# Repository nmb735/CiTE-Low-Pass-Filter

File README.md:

# 🎚️ CiTE: Fourth Order Low Pass Filter

Full implementation of a fourth-order low-pass filter. The circuit design is based on the use of two cascaded second-order Sallen-Key configurations. Presented as the final project for CiTE (*Circuits i Tecnologies Electròniques*), part of the third course of the Electronic Engineering degree (BSc).

## 👨‍💻 Developers

- Adrià Arús - @Addruss
- Nedal Benelmekki - @nmb735
- Marc Serra - @Marcits

## 📋 Context and Introduction

- This project involves the full implementation of a fourth-order low-pass filter. The circuit design is based on the use of two cascaded second-order Sallen-Key configurations. It was presented as the final project for CiTE (*Circuits i Tecnologies Electròniques*), part of the third course of the Electronic Engineering degree (BSc).

- The project encompassed the entire process, including circuit and PCB design, manufacturing, soldering, and testing.

## 📂 Content

This repository contains the full project in different directories:

1. **`EAGLE Project`**: Full PCB project (`EAGLE` software, from Autodesk), including Layout, Schematic, Gerber Files, BOM, and other related files.
2. **`Documentation`**: Project documentation and presentation poster.

## 📝 License

This project is licensed under the MIT License. See the LICENSE file for more details.

## ⚠️ Disclaimer

This project is provided for educational purposes only. The authors are not responsible for any use of this project in any form of academic dishonesty or plagiarism. Please adhere to your institution's academic integrity policies when using or referencing this project.

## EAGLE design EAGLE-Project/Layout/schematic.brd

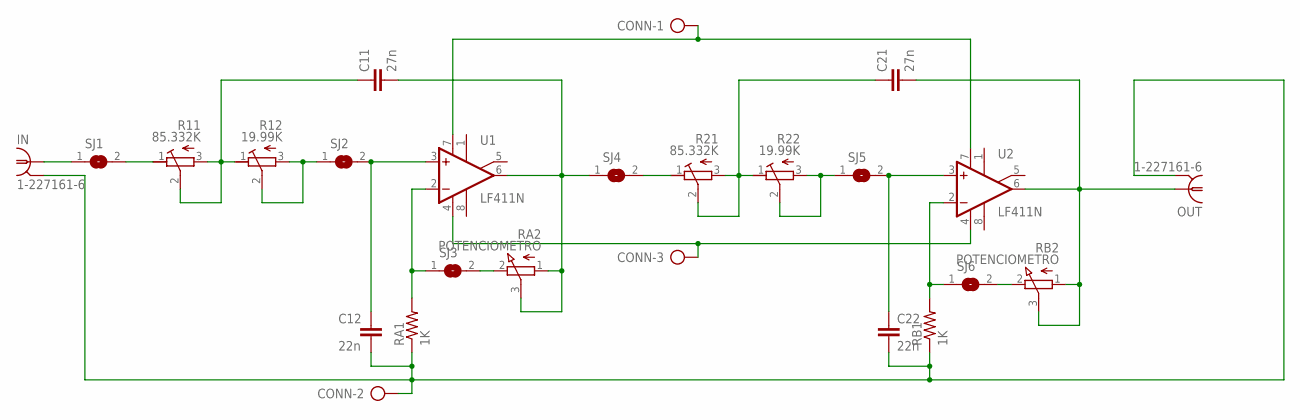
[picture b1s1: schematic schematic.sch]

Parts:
C11, C21: 27n; C050-025X075
C12, C22: 22n; C050-025X075
CONN: AK500/3
IN: 1-227161-6; AMP_227161
OUT: 1-227161-6; AMP_227161
R11, R21: 85.332K; RTRIMT93YB
R12, R22: 19.99K; RTRIMT93YB
RA1: 1K; 0207/10
RA2: POTENCIOMETRO; TSM4YJ
RB1: 1K; 0207/10
RB2: POTENCIOMETRO; TSM4YJ
SJ1, SJ2, SJ3, SJ4, SJ5, SJ6: SJW
U1, U2: LF411N; DIL08

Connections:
unnamed: IN.1, SJ1.1
unnamed: R11.1 (E), SJ1.2
unnamed: C11.1, R11.2 (S), R11.3 (A), R12.1 (E)
unnamed: R12.2 (S), R12.3 (A), SJ2.1
unnamed: C12.1, SJ2.2, U1.3 (+IN)
unnamed: RA1.2, SJ3.1, U1.2 (-IN)
unnamed: C12.2, C22.2, CONN.2, IN.2, OUT.2, RA1.1, RB1.1
unnamed: C11.2, RA2.1 (A), RA2.3 (S), SJ4.1, U1.6 (OUT)
unnamed: R21.1 (E), SJ4.2
unnamed: RA2.2 (E), SJ3.2
unnamed: C21.1, R21.2 (S), R21.3 (A), R22.1 (E)
unnamed: R22.2 (S), R22.3 (A), SJ5.1
unnamed: C22.1, SJ5.2, U2.3 (+IN)
unnamed: C21.2, OUT.1, RB2.1 (A), RB2.3 (S), U2.6 (OUT)
unnamed: RB1.2, SJ6.1, U2.2 (-IN)
unnamed: RB2.2 (E), SJ6.2
unnamed: CONN.1, U1.7 (V+), U2.7 (V+)
unnamed: CONN.3, U1.4 (V-), U2.4 (V-)

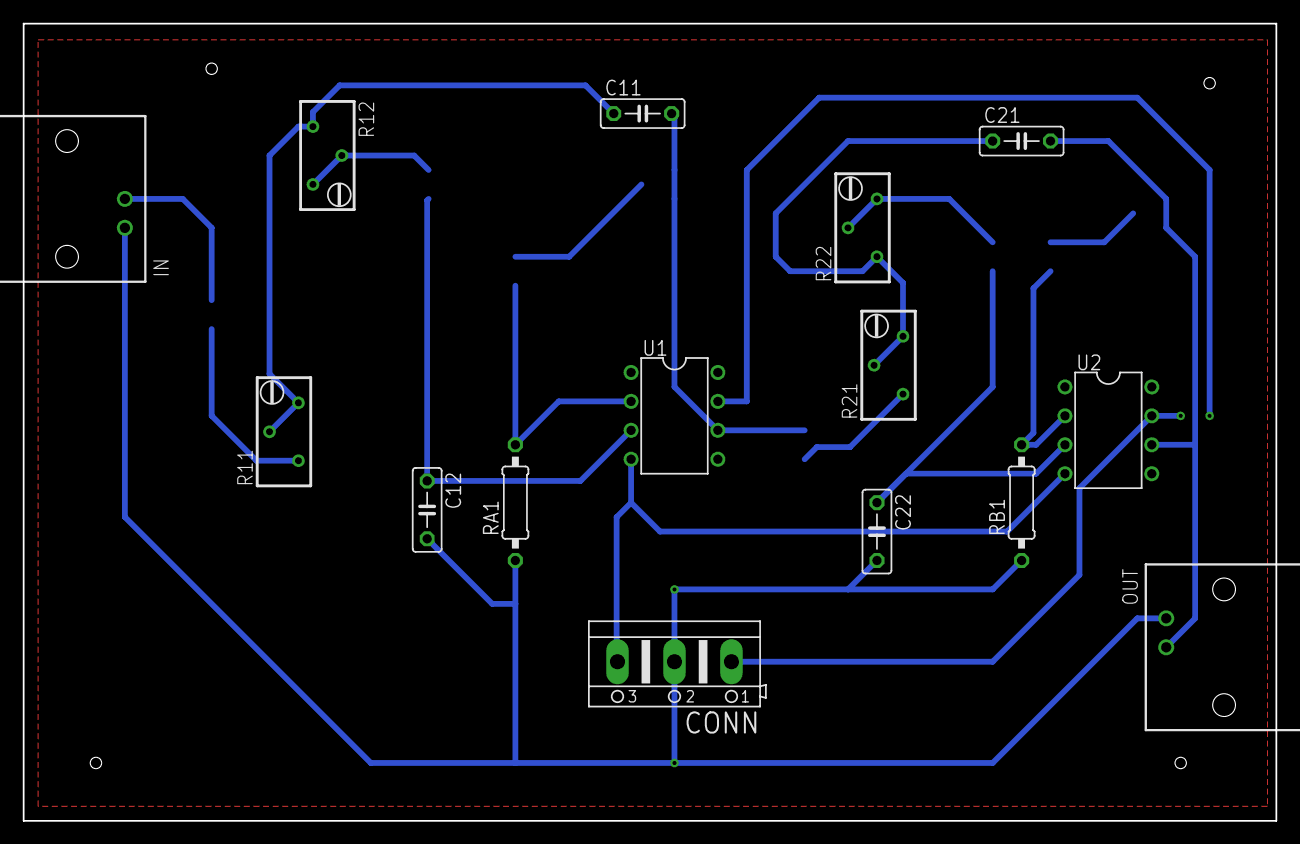
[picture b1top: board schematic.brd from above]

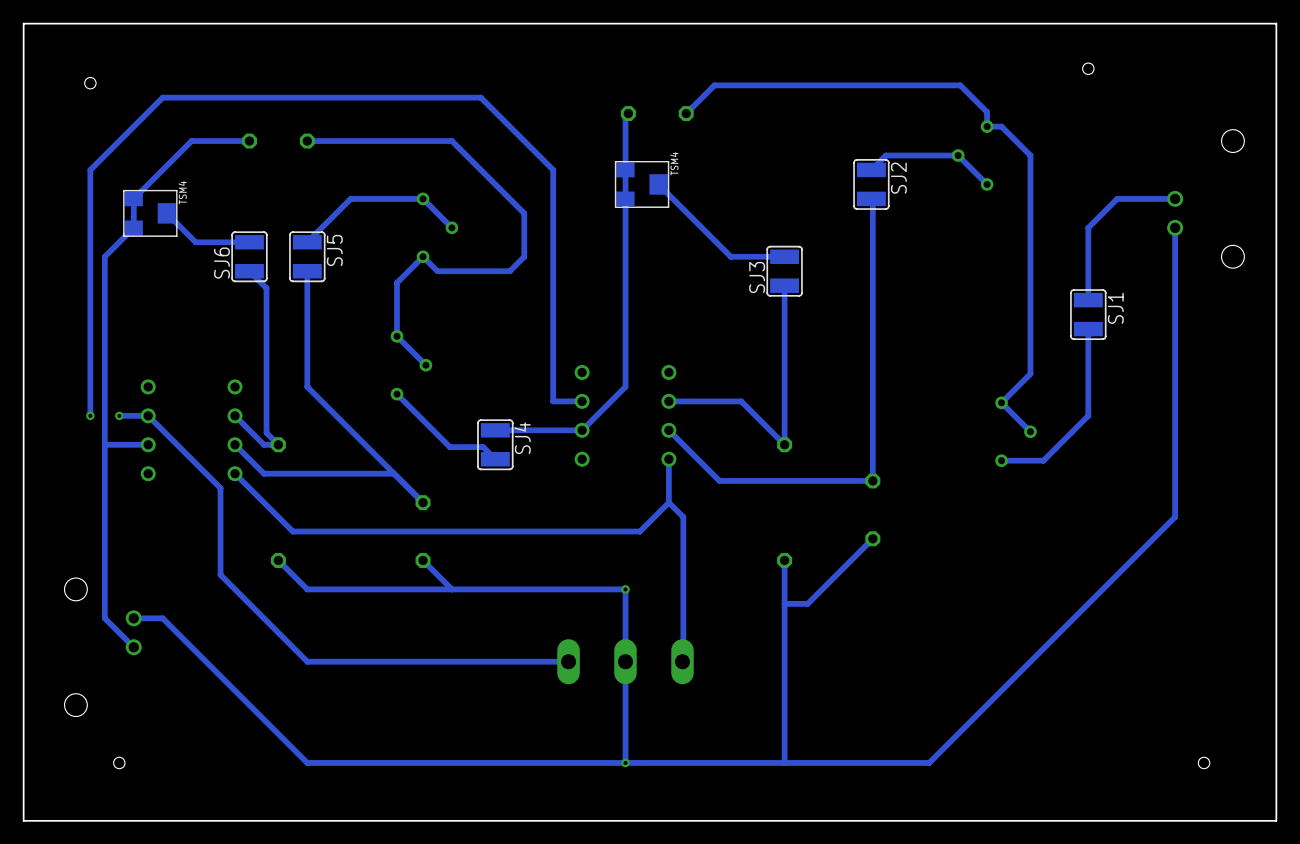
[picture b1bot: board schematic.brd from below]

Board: 2 copper layers, 110.0 x 70.0 mm, 23 parts (8 on the bottom side), 18 nets.

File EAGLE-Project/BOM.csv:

"Part";"Value";"Device";"Package";"Description";"MF";"MPN";"OC_FARNELL";"OC_NEWARK";"POPULARITY";"SPICEMODEL";"SPICEPREFIX";"SPICEPREFIXL";
"C11";"27n";"C-EU050-025X075";"C050-025X075";"CAPACITOR, European symbol";"";"";"";"";"29";"";"C";"";
"C12";"22n";"C-EU050-025X075";"C050-025X075";"CAPACITOR, European symbol";"";"";"";"";"29";"";"C";"";
"C21";"27n";"C-EU050-025X075";"C050-025X075";"CAPACITOR, European symbol";"";"";"";"";"29";"";"C";"";
"C22";"22n";"C-EU050-025X075";"C050-025X075";"CAPACITOR, European symbol";"";"";"";"";"29";"";"C";"";
"CONN";"";"AK500/3";"AK500/3";"CONNECTOR";"";"";"unknown";"unknown";"3";"";"";"";
"IN";"1-227161-6";"1-227161-6";"AMP_227161";"JACK,  RIGHT ANGLE, 50 OHM, PCB, BNC";"TYCO ELECTRONICS";"1-227161-6";"unknown";"09H7854";"0";"";"";"";
"OUT";"1-227161-6";"1-227161-6";"AMP_227161";"JACK,  RIGHT ANGLE, 50 OHM, PCB, BNC";"TYCO ELECTRONICS";"1-227161-6";"unknown";"09H7854";"0";"";"";"";
"R11";"85.332K";"R-TRIMMT93YB";"RTRIMT93YB";"Trimm resistor";"";"";"";"";"0";"X";"";"POT";
"R12";"19.99K";"R-TRIMMT93YB";"RTRIMT93YB";"Trimm resistor";"";"";"";"";"0";"X";"";"POT";
"R21";"85.332K";"R-TRIMMT93YB";"RTRIMT93YB";"Trimm resistor";"";"";"";"";"0";"X";"";"POT";
"R22";"19.99K";"R-TRIMMT93YB";"RTRIMT93YB";"Trimm resistor";"";"";"";"";"0";"X";"";"POT";
"RA1";"1K";"R-US_0207/10";"0207/10";"RESISTOR, American symbol";"";"";"";"";"36";"";"R";"";
"RA2";"POTENCIOMETRO";"POTENCIOMETRO";"TSM4YJ";"";"";"";"";"";"";"";"";"";
"RB1";"1K";"R-US_0207/10";"0207/10";"RESISTOR, American symbol";"";"";"";"";"36";"";"R";"";
"RB2";"POTENCIOMETRO";"POTENCIOMETRO";"TSM4YJ";"";"";"";"";"";"";"";"";"";
"SJ1";"";"SJW";"SJW";"SMD solder JUMPER";"";"";"";"";"3";"";"";"";
"SJ2";"";"SJW";"SJW";"SMD solder JUMPER";"";"";"";"";"3";"";"";"";
"SJ3";"";"SJW";"SJW";"SMD solder JUMPER";"";"";"";"";"3";"";"";"";
"SJ4";"";"SJW";"SJW";"SMD solder JUMPER";"";"";"";"";"3";"";"";"";
"SJ5";"";"SJW";"SJW";"SMD solder JUMPER";"";"";"";"";"3";"";"";"";
"SJ6";"";"SJW";"SJW";"SMD solder JUMPER";"";"";"";"";"3";"";"";"";
"U1";"LF411N";"LF411N";"DIL08";"OP AMP";"";"";"";"";"0";"";"";"";
"U2";"LF411N";"LF411N";"DIL08";"OP AMP";"";"";"";"";"0";"";"";"";

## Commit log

2024-06-30 docs: readme file
2024-06-30 chore: files
